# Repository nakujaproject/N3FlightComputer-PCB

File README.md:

# N3FlightComputer
Electrical design for N3 flight computer

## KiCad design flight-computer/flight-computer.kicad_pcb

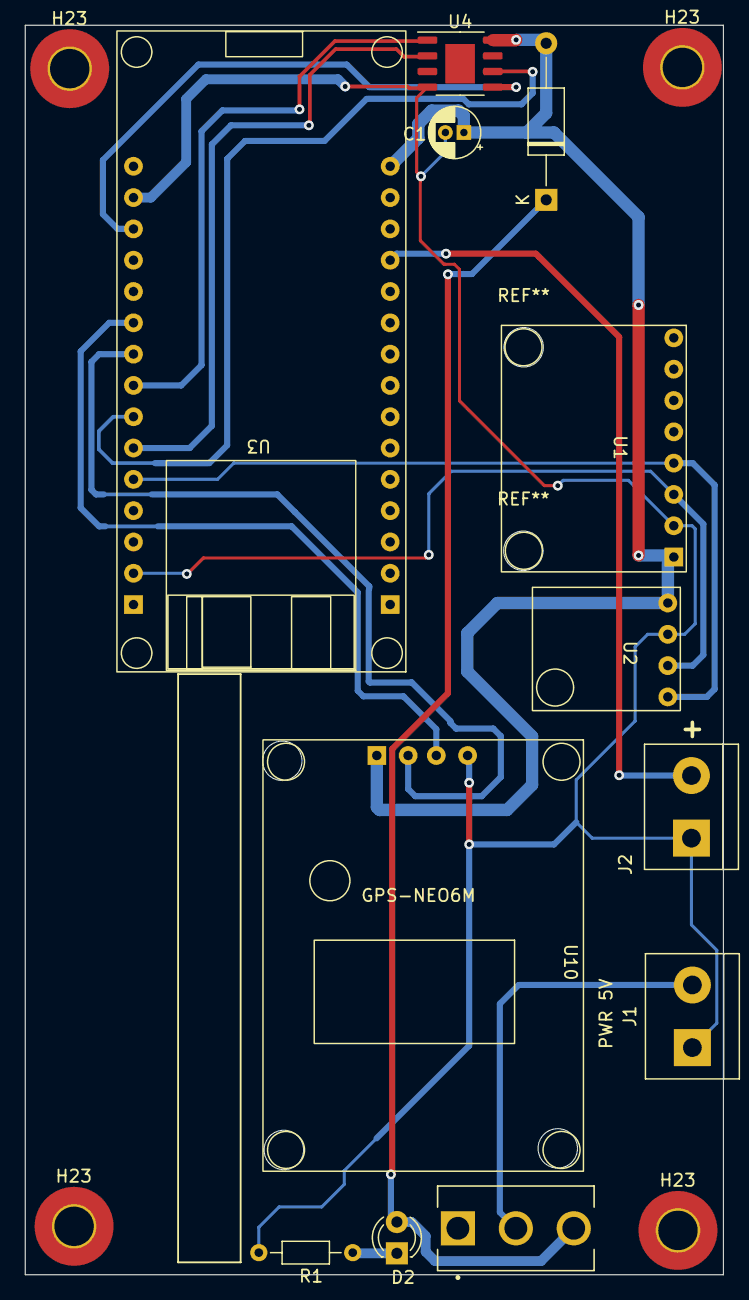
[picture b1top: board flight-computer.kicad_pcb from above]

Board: 2 copper layers, 56.6 x 101.4 mm, 16 parts (0 on the bottom side), 14 nets.

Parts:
C1: 100nF; CP_Radial_D4.0mm_P1.50mm
D1: DIODE; D_A-405_P12.70mm_Horizontal
D2: LED; LED_D3.0mm
H23, H23#2, H23#3, H23#4: MountingHole_Pad; MountingHole_3.2mm_M3_Pad_TopOnly
J1: PWR 5V; TerminalBlock_bornier-2_P5.08mm
J2: Screw_Terminal_01x02; TerminalBlock_bornier-2_P5.08mm
R1: R; R_Axial_DIN0204_L3.6mm_D1.6mm_P7.62mm_Horizontal
S1: 100SP1T1B4M2QE; SW_100SP1T1B4M2QE
U1: MPU6050
U2: BMP180
U3: ESP32_DEVKIT
U4: W25Q64FV_Winbond_Flash_Memory; HTSOP-8-1EP_3.9x4.9mm_P1.27mm_EP2.4x3.2mm
U10: GPS-NEO6M

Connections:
+5V: C1.1, D1.2 (A), U1.1 (VCC), U2.4 (VCC), U3.16 (VIN), U4.8 (VCC), U10.1 (VCC)
ACTIVATE_EJECT: J2.2, U3.13 (D12)
CLK: U3.32 (D18), U4.6 (CLK)
CS: U3.31 (D5), U4.1 (CS)
D0: U3.33 (D19), U4.2 (D0)
DI: U3.26 (D15), U4.5 (DI)
GND: C1.2, J1.1, J2.1, R1.2, U1.2 (GND), U2.3 (GND), U3.25 (GND), U4.4 (GND), U10.4 (GND)
GPS_RX: U3.30 (TX2), U10.2 (RX)
GPS_TX: U3.29 (RX2), U10.3 (TX)
unnamed: D1.1 (K), D2.2 (A), S1.3
unnamed: D2.1 (K), R1.1
unnamed: J1.2, S1.2
SCL: U1.3 (SCL), U2.2 (SCL), U3.37 (D22)
SDA: U1.4 (SDA), U2.1 (SDA), U3.34 (D21)

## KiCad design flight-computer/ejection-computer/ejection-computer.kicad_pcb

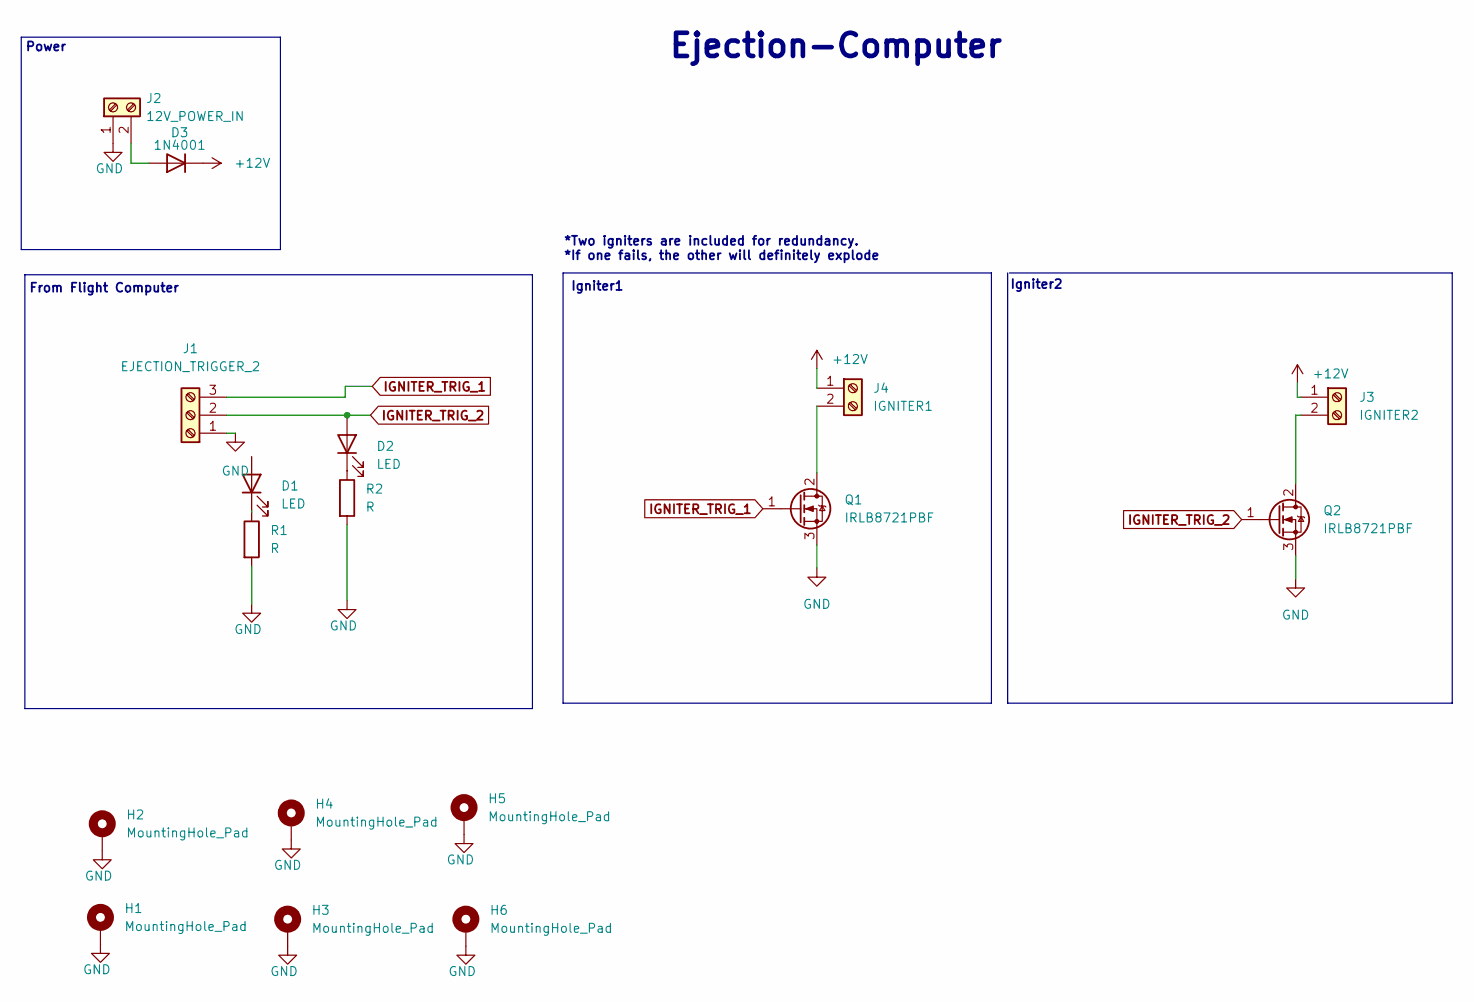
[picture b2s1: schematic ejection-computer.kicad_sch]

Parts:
D1, D2: LED; LED_0805_2012Metric
D3: 1N4001; D_0805_2012Metric
H1, H2, H3, H4, H5, H6: MountingHole_Pad; MountingHole_3.2mm_M3_Pad_Via
J1: EJECTION_TRIGGER_2; TerminalBlock_bornier-3_P5.08mm
J2: 12V_POWER_IN; TerminalBlock_bornier-2_P5.08mm
J3: IGNITER2; TerminalBlock_bornier-2_P5.08mm
J4: IGNITER1; TerminalBlock_bornier-2_P5.08mm
Q1, Q2: IRLB8721PBF; TO-220-3_Vertical
R1, R2: R; LED_0805_2012Metric

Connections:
+12V: D3.1 (K), J3.1, J4.1
GND: H1.1, H2.1, H3.1, H4.1, H5.1, H6.1, J1.1, J2.1, Q1.3 (S), Q2.3 (S), R1.2, R2.2
IGNITER_TRIG_1: J1.3, Q1.1 (G)
IGNITER_TRIG_2: D2.2 (A), J1.2, Q2.1 (G)
unnamed: D1.1 (K), R1.1
unnamed: D2.1 (K), R2.1
unnamed: D3.2 (A), J2.2
unnamed: J3.2, Q2.2 (D)
unnamed: J4.2, Q1.2 (D)

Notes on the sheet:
From Flight Computer
Igniter2
Ejection-Computer
Power
*Two igniters are included for redundancy. *If one fails, the other will definitely explode
Igniter1

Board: 2 copper layers, 17 parts (0 on the bottom side), 9 nets, no tracks yet.

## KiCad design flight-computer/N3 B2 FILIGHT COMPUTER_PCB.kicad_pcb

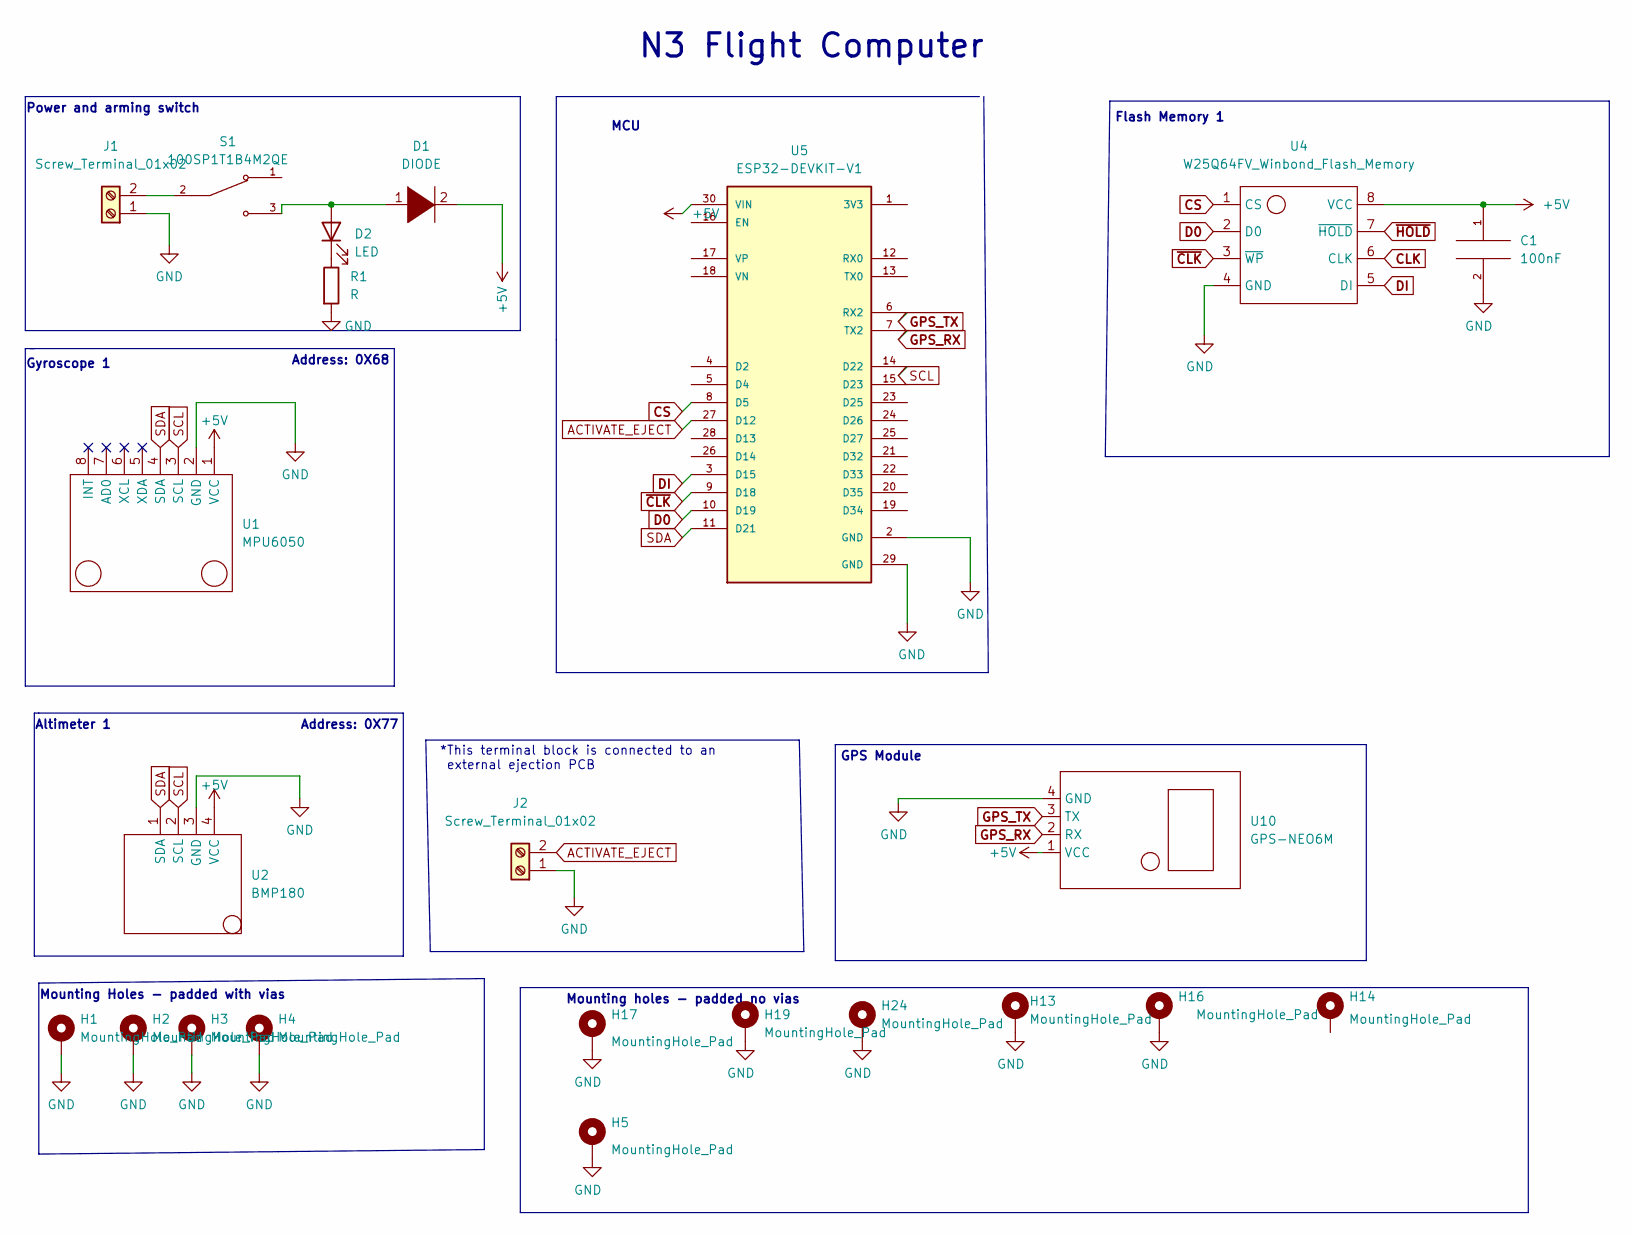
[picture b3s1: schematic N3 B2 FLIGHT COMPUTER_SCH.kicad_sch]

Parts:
C1: 100nF; C_0805_2012Metric
D1: DIODE; D_A-405_P12.70mm_Horizontal
D2: LED; LED_0805_2012Metric
H1, H2, H3, H4: MountingHole_Pad; MountingHole_3.2mm_M3_Pad_Via
H5, H13, H14, H16, H17, H19, H24: MountingHole_Pad; MountingHole_3.2mm_M3_Pad_TopOnly
J1, J2: Screw_Terminal_01x02; TerminalBlock_bornier-2_P5.08mm
R1: R; R_0805_2012Metric
S1: 100SP1T1B4M2QE; SW_100SP1T1B4M2QE; PARTREV E
U1: MPU6050
U2: BMP180
U4: W25Q64FV_Winbond_Flash_Memory; HTSOP-8-1EP_3.9x4.9mm_P1.27mm_EP2.4x3.2mm
U5: ESP32-DEVKIT-V1; MODULE_ESP32_DEVKIT_V1; PARTREV N/A
U10: GPS-NEO6M

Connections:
+5V: C1.1, D1.2 (A), U1.1 (VCC), U2.4 (VCC), U4.8 (VCC), U5.30 (VIN), U10.1 (VCC)
ACTIVATE_EJECT: J2.2, U5.27 (D12)
CLK: U4.6 (CLK)
CS: U4.1 (CS), U5.8 (D5)
D0: U4.2 (D0), U5.10 (D19)
DI: U4.5 (DI), U5.3 (D15)
GND: C1.2, H1.1, H2.1, H3.1, H4.1, H5.1, H13.1, H16.1, H17.1, H19.1, H24.1, J1.1, J2.1, R1.2, U1.2 (GND), U2.3 (GND), U4.4 (GND), U5.2 (GND), U5.29 (GND), U10.4 (GND)
GPS_RX: U5.7 (TX2), U10.2 (RX)
GPS_TX: U5.6 (RX2), U10.3 (TX)
unnamed: D1.1 (K), D2.2 (A), S1.3
unnamed: D2.1 (K), R1.1
unnamed: J1.2, S1.2
SCL: U1.3 (SCL), U2.2 (SCL), U5.14 (D22)
SDA: U1.4 (SDA), U2.1 (SDA), U5.11 (D21)
~CLK: U4.3 (~WP), U5.9 (D18)
~HOLD: U4.7 (~HOLD)

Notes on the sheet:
MCU
Address: 0X68
N3 Flight Computer
Gyroscope 1
Mounting Holes - padded with vias
*This terminal block is connected to an external ejection PCB
GPS Module
Address: 0X77
Altimeter 1
Mounting holes - padded no vias
Power and arming switch
Flash Memory 1

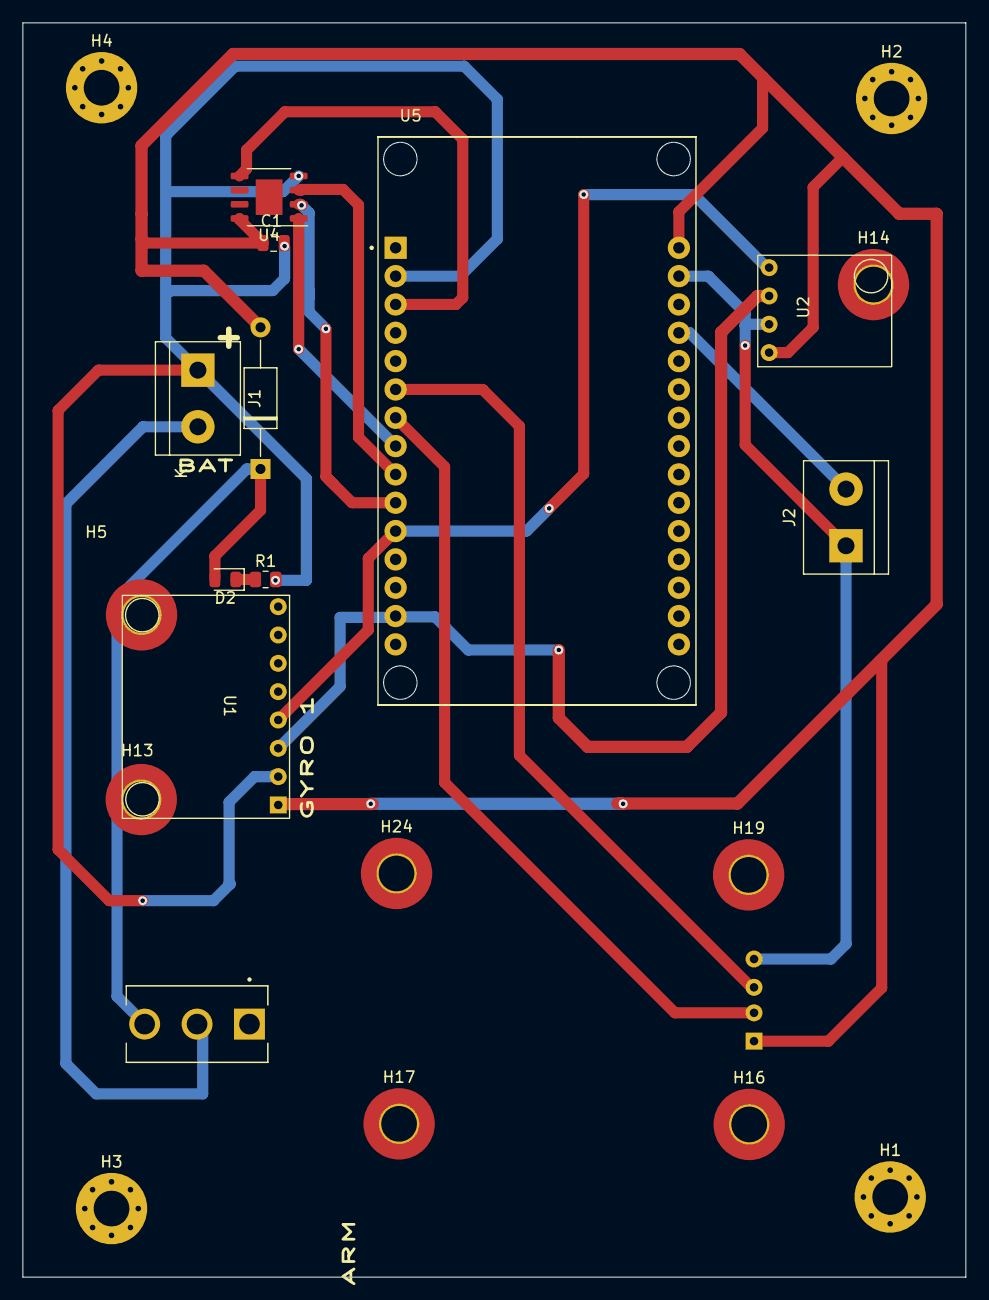
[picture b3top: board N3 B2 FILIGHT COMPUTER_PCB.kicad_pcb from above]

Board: 2 copper layers, 84.6 x 112.5 mm, 23 parts (1 on the bottom side), 14 nets.

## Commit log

2023-02-03 added Flash memory symbol from modules
2023-02-03 added PCB footprints for altimeter and gyroscope
2023-02-07 added mounting holes for sensors
2023-02-07 added NEO6M GPS footprint
2023-03-02 this design is subject to change
2023-03-02 removed redundancy
2023-03-15 added pcb pdfs
2023-06-05 Add files via upload
    This designs are subject to change
    Adjustments made: changing ESP footprint, reduced number of sensors to one each, routing, board dimensions
2023-10-10 The new FC Designs
2023-10-11 Newly Updated Flight Computer
2023-10-18 Newly Updated
2023-10-24 The updated FC
2023-10-24 The newly updated FCs
2024-01-18 Ejection Board
2024-01-25 The updated PCB Files
2024-01-25 WiFi FC 2024
2024-01-25 README.md
2024-01-26 Updated WiFi FC
